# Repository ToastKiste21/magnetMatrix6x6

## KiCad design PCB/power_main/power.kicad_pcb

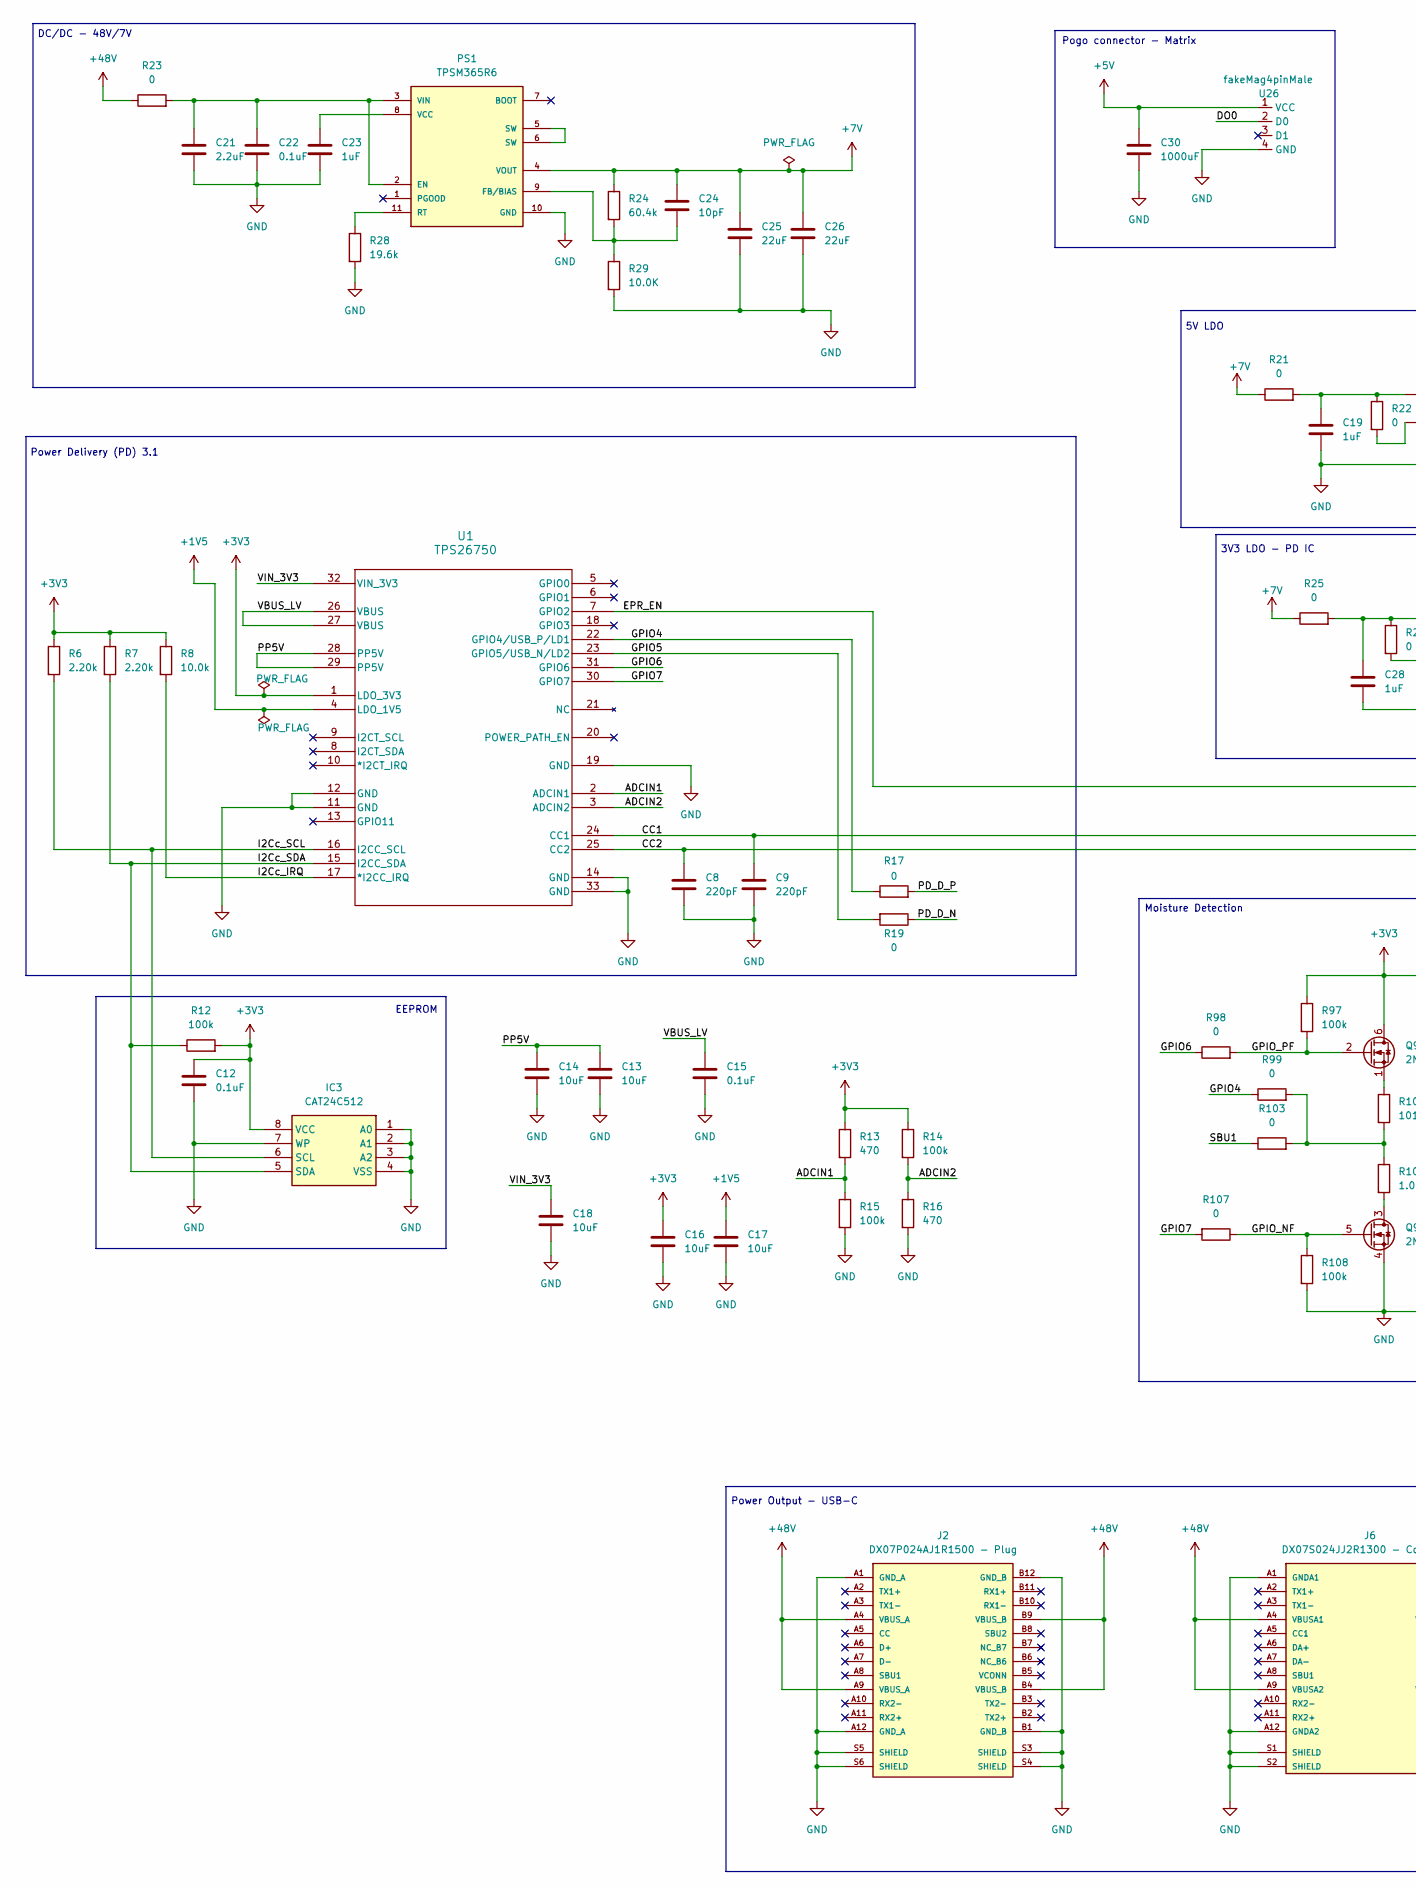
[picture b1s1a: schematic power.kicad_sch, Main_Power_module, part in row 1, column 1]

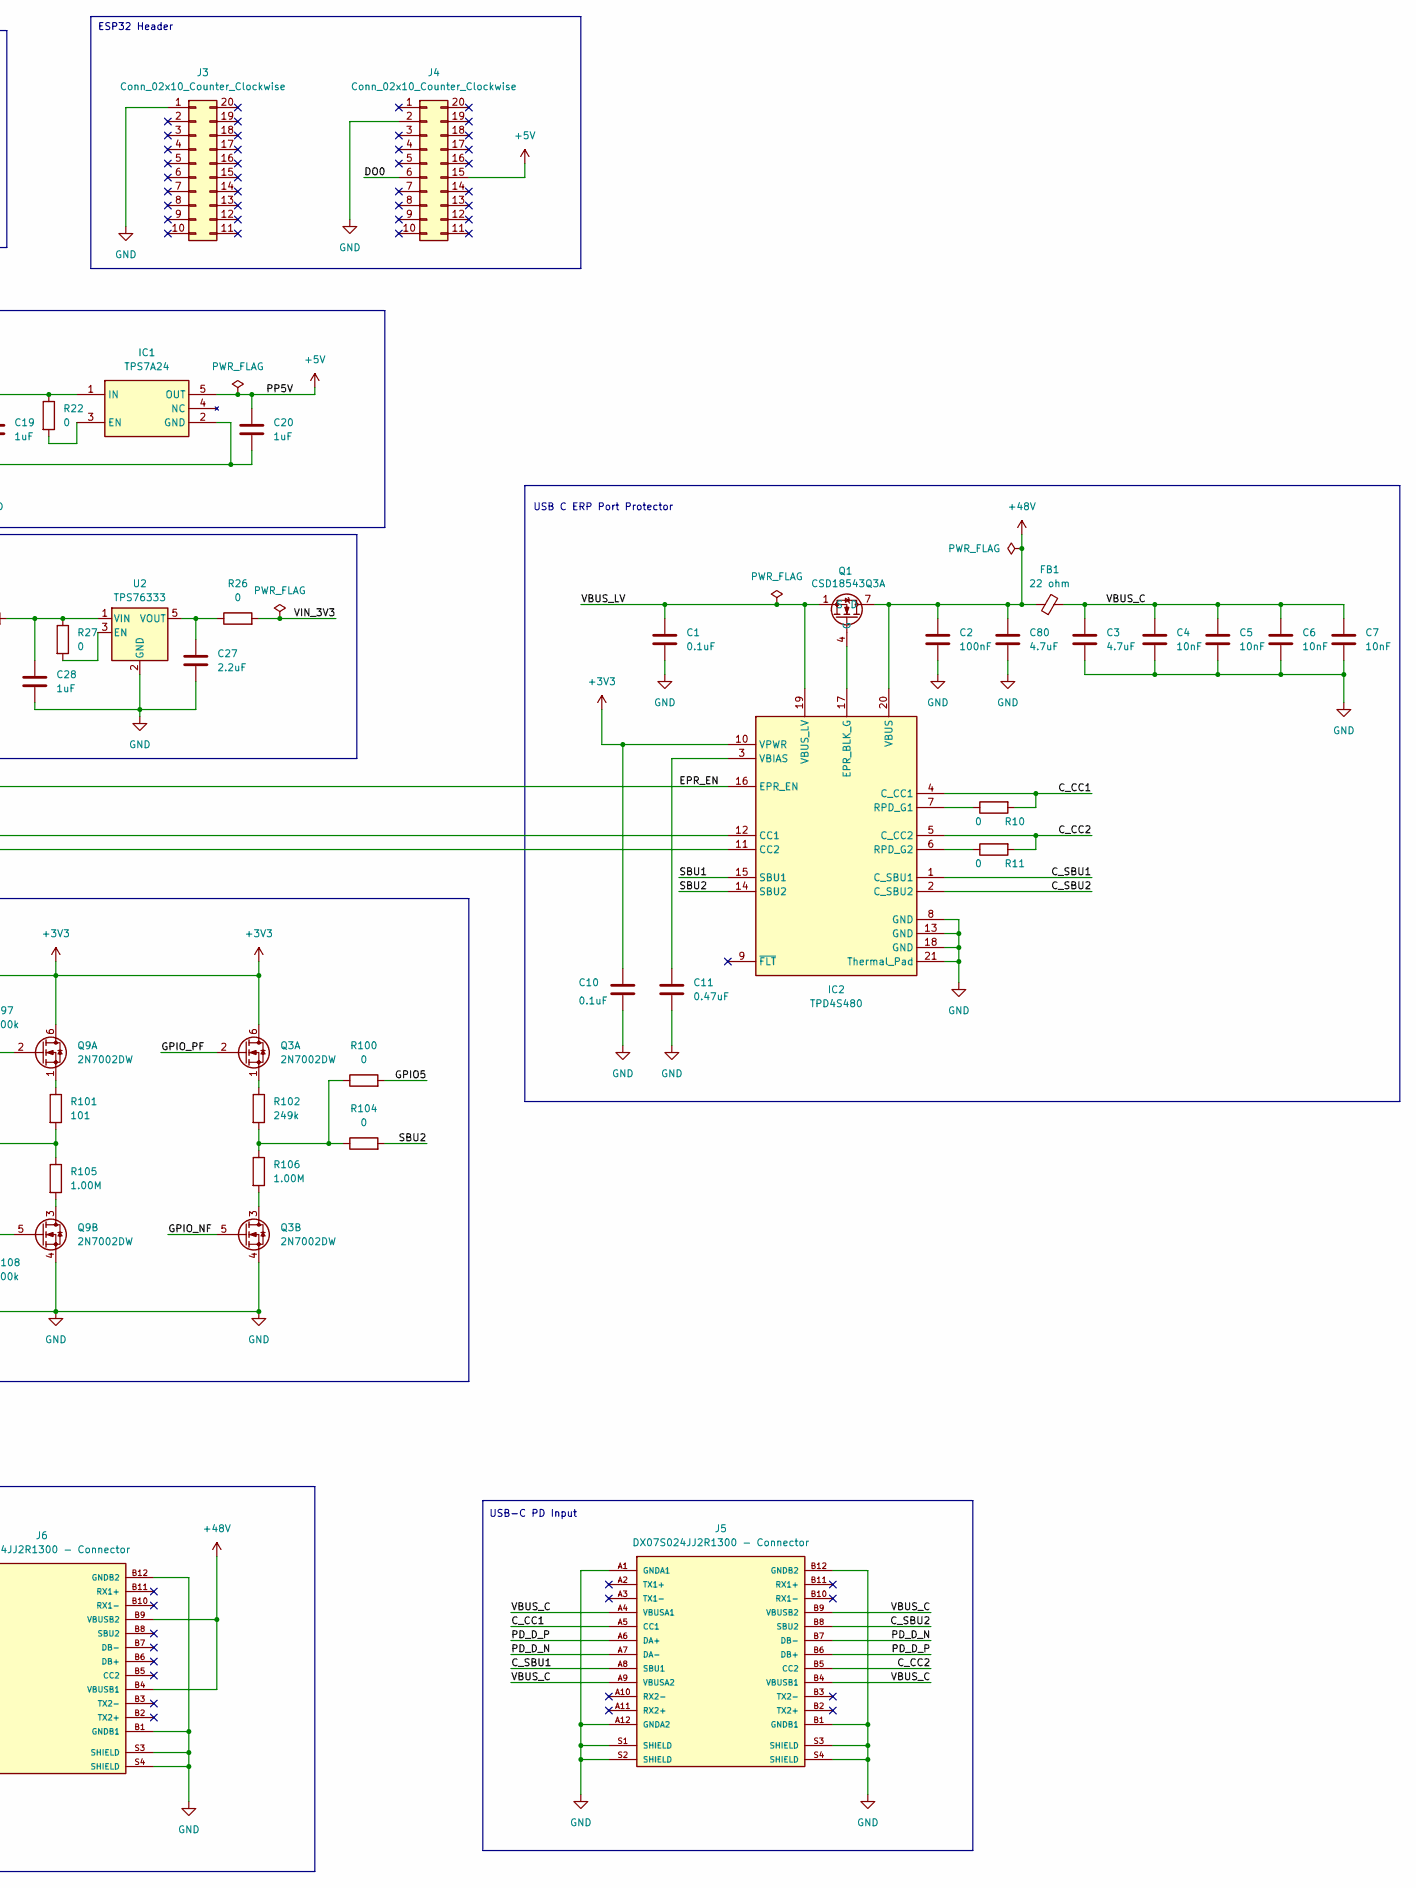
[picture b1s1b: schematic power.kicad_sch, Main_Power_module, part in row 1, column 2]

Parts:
C1, C10, C12, C15, C22: 0.1uF; C_0402_1005Metric
C2: 100nF; C_0201_0603Metric
C3, C80: 4.7uF; C_0805_2012Metric
C4, C5, C6, C7: 10nF; C_0603_1608Metric
C8, C9: 220pF; C_0201_0603Metric
C11: 0.47uF; C_0603_1608Metric
C13, C14: 10uF; C_0603_1608Metric
C16, C17, C18: 10uF; C_0402_1005Metric
C19, C20, C28: 1uF; C_0805_2012Metric
C21: 2.2uF; C_1206_3216Metric
C23: 1uF; C_0402_1005Metric
C24: 10pF; C_0402_1005Metric
C25, C26: 22uF; C_0603_1608Metric
C27: 2.2uF; C_0603_1608Metric
C30: 1000uF; CP_EIA-7343-15_Kemet-W
FB1: 22 ohm; L_0805_2012Metric
IC1: TPS7A24; SOT95P280X145-5N; Manufacturer_Part_Number TPS7A2450DBVR; Mouser Part Number 595-TPS7A2450DBVR
IC2: TPD4S480; QFN40P300X300X80-21N-D; Manufacturer_Part_Number TPD4S480RUKR
IC3: CAT24C512; SOIC127P600X175-8N; Manufacturer_Part_Number CAT24C512WI-GT3; Mouser Part Number 863-CAT24C512WI-GT3
J2: DX07P024AJ1R1500 - Plug; JAE_DX07P024AJ1R1500; PARTREV January 2016
J3, J4: Conn_02x10_Counter_Clockwise; PinHeader_2x10_P2.54mm_Vertical
J5, J6: DX07S024JJ2R1300 - Connector; JAE_DX07S024JJ2R1300; PARTREV 3
PS1: TPSM365R6; CONV_TPSM365R15RDNR; PARTREV A
Q1: CSD18543Q3A; Manufacturer_Part_Number CSD18543Q3A; Mouser Part Number 595-CSD18543Q3A
Q3, Q9: 2N7002DW; SOT-363_SC-70-6
R6, R7: 2.20k; R_0402_1005Metric
R8: 10.0k; R_0402_1005Metric
R10, R11, R17, R19, R21, R22, R23, R25, R26, R27: 0; R_0201_0603Metric
R12: 100k; R_0201_0603Metric
R13, R16: 470; R_0603_1608Metric
R14, R15: 100k; R_0603_1608Metric
R24: 60.4k; R_0603_1608Metric
R28: 19.6k; R_0402_1005Metric
R29: 10.0K; R_0402_1005Metric
R97, R108: 100k; R_0402_1005Metric
R98, R99, R100, R103, R104, R107: 0; R_0402_1005Metric
R101: 101; R_0603_1608Metric
R102: 249k; R_0603_1608Metric
R105, R106: 1.00M; R_0402_1005Metric
U1: TPS26750; VQFN32_RSM_TEX
U2: TPS76333; SOT-23-5
U26: fakeMag4pinMale; fakemag4pin90degMale; MPN MG0422F-RA

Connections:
+1V5: C17.1, U1.4 (LDO_1V5)
+3V3: C10.1, C12.1, C16.1, IC2.10 (VPWR), IC3.8 (VCC), Q3.6 (D), Q9.6 (D), R6.1, R7.1, R8.1, R12.2, R13.1, R14.1, R97.1, U1.1 (LDO_3V3)
+5V: C13.1, C14.1, C20.1, C30.1, IC1.5 (OUT), J4.15, U1.28 (PP5V), U1.29 (PP5V), U26.1 (VCC)
+7V: C24.1, C25.1, C26.1, PS1.4 (VOUT), PS1.4_1, PS1.4_2, PS1.4_3, PS1.4_4, PS1.4_5, R21.1, R24.1, R25.1
+48V: C2.1, C80.1, FB1.1, IC2.20 (VBUS), J2.A4 (VBUS_A), J2.A9 (VBUS_A), J2.B4 (VBUS_B), J2.B9 (VBUS_B), J6.A4 (VBUSA1), J6.A9 (VBUSA2), J6.B4 (VBUSB1), J6.B9 (VBUSB2), Q1.5 (D), Q1.6 (D), Q1.7 (D), Q1.8 (D), Q1.9 (D), R23.1
/ADCIN1: R13.2, R15.1, U1.2 (ADCIN1)
/ADCIN2: R14.2, R16.1, U1.3 (ADCIN2)
/CC1: C9.1, IC2.12 (CC1), U1.24 (CC1)
/CC2: C8.1, IC2.11 (CC2), U1.25 (CC2)
/C_CC1: IC2.4 (C_CC1), J5.A5 (CC1), R10.2
/C_CC2: IC2.5 (C_CC2), J5.B5 (CC2), R11.2
/C_SBU1: IC2.1 (C_SBU1), J5.A8 (SBU1)
/C_SBU2: IC2.2 (C_SBU2), J5.B8 (SBU2)
/DO0: J4.6, U26.2 (D0)
/EPR_EN: IC2.16 (EPR_EN), U1.7 (GPIO2)
/GPIO4: R17.1, R99.1, U1.22 (GPIO4/USB_P/LD1)
/GPIO5: R19.2, R100.2, U1.23 (GPIO5/USB_N/LD2)
/GPIO6: R98.1, U1.31 (GPIO6)
/GPIO7: R107.2, U1.30 (GPIO7)
/GPIO_NF: Q3.5 (G), Q9.5 (G), R107.1, R108.1
/GPIO_PF: Q3.2 (G), Q9.2 (G), R97.2, R98.2
/I2Cc_IRQ: R8.2, U1.17 (*I2CC_IRQ)
/I2Cc_SCL: IC3.6 (SCL), R6.2, U1.16 (I2CC_SCL)
/I2Cc_SDA: IC3.5 (SDA), R7.2, R12.1, U1.15 (I2CC_SDA)
/PD_D_N: J5.A7 (DA-), J5.B7 (DB-), R19.1
/PD_D_P: J5.A6 (DA+), J5.B6 (DB+), R17.2
/SBU1: IC2.15 (SBU1), R103.1
/SBU2: IC2.14 (SBU2), R104.2
/VBUS_C: C3.1, C4.1, C5.1, C6.1, C7.1, FB1.2, J5.A4 (VBUSA1), J5.A9 (VBUSA2), J5.B4 (VBUSB1), J5.B9 (VBUSB2)
/VBUS_LV: C1.1, C15.1, IC2.19 (VBUS_LV), Q1.1 (S), Q1.2 (S), Q1.3 (S), U1.26 (VBUS), U1.27 (VBUS)
/VIN_3V3: C18.1, R26.2, U1.32 (VIN_3V3)
GND: C1.2, C2.2, C3.2, C4.2, C5.2, C6.2, C7.2, C8.2, C9.2, C10.2, C11.2, C12.2, C13.2, C14.2, C15.2, C16.2, C17.2, C18.2, C19.2, C20.2, C21.2, C22.2, C23.2, C25.2, C26.2, C27.2, C28.2, C30.2, C80.2, IC1.2 (GND), IC2.8 (GND), IC2.13 (GND), IC2.18 (GND), IC2.21 (Thermal_Pad), IC3.1 (A0), IC3.2 (A1), IC3.3 (A2), IC3.4 (VSS), IC3.7 (WP), J2.A1 (GND_A), J2.A12 (GND_A), J2.B1 (GND_B), J2.B12 (GND_B), J2.S3 (SHIELD), J2.S4 (SHIELD), J2.S5 (SHIELD), J2.S6 (SHIELD), J3.1 (GND), J4.2, J5.A1 (GNDA1), J5.A12 (GNDA2), J5.B1 (GNDB1), J5.B12 (GNDB2), J5.S1 (SHIELD), J5.S2 (SHIELD), J5.S3 (SHIELD), J5.S4 (SHIELD), J6.A1 (GNDA1), J6.A12 (GNDA2), J6.B1 (GNDB1), J6.B12 (GNDB2), J6.S1 (SHIELD), J6.S2 (SHIELD), J6.S3 (SHIELD), J6.S4 (SHIELD), PS1.10 (GND), PS1.10_1, PS1.10_2, PS1.10_3, PS1.10_4, PS1.10_5, Q3.4 (S), Q9.4 (S), R15.2, R16.2, R28.2, R29.2, R108.2, U1.11 (GND), U1.12 (GND), U1.14 (GND), U1.19 (GND), U1.33 (GND), U2.2 (GND), U26.4 (GND)
unnamed: IC1.3 (EN), R22.2
unnamed: C19.1, IC1.1 (IN), R21.2, R22.1
unnamed: IC2.17 (EPR_BLK_G), Q1.4 (G)
unnamed: IC2.7 (RPD_G1), R10.1
unnamed: IC2.6 (RPD_G2), R11.1
unnamed: C11.1, IC2.3 (VBIAS)
unnamed: C21.1, C22.1, PS1.2 (EN), PS1.3 (VIN), PS1.3_1, R23.2
unnamed: C24.2, PS1.9 (FB/BIAS), R24.2, R29.1
unnamed: PS1.11 (RT), R28.1
unnamed: PS1.5 (SW), PS1.5_1, PS1.5_2, PS1.5_3, PS1.5_4, PS1.5_5, PS1.6 (SW), PS1.6_1, PS1.6_2
unnamed: C23.1, PS1.8 (VCC)
unnamed: Q3.1 (S), R102.1
unnamed: Q3.3 (D), R106.2
unnamed: Q9.1 (S), R101.1
unnamed: Q9.3 (D), R105.2
unnamed: R100.1, R102.2, R104.1, R106.1
unnamed: R99.2, R101.2, R103.2, R105.1
unnamed: R27.2, U2.3 (EN)
unnamed: C28.1, R25.2, R27.1, U2.1 (VIN)
unnamed: C27.1, R26.1, U2.5 (VOUT)

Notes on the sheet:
Power Output - USB-C
DC/DC - 48V/7V
USB C ERP Port Protector
Power Delivery (PD) 3.1
5V LDO
Pogo connector - Matrix
3V3 LDO - PD IC
EEPROM
ESP32 Header
USB-C PD Input
Moisture Detection

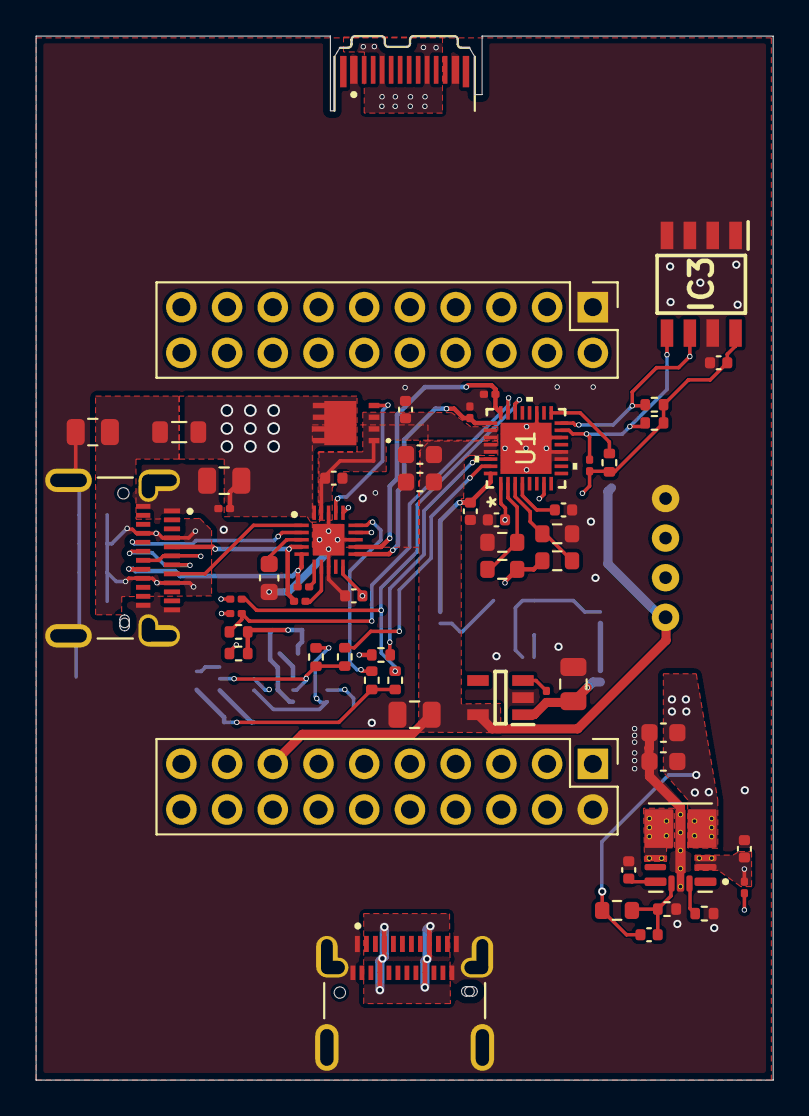
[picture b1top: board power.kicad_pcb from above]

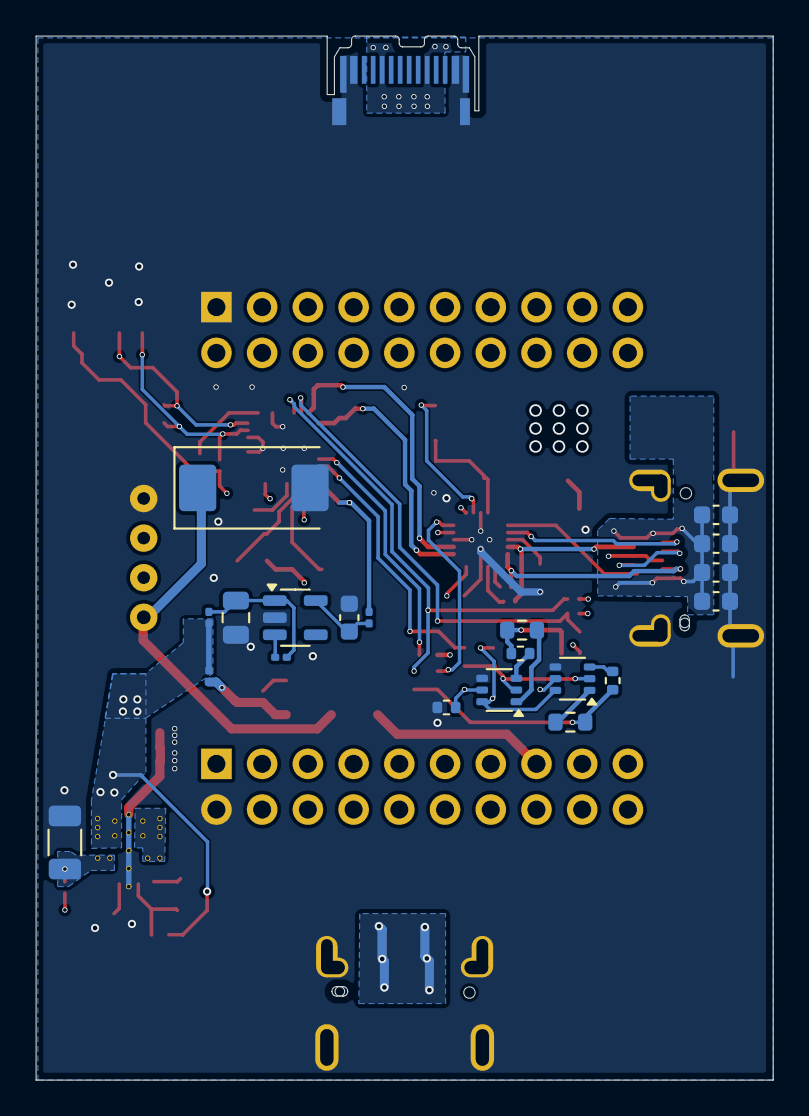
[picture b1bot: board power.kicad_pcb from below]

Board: 4 copper layers, 40.9 x 58.0 mm, 79 parts (20 on the bottom side), 52 nets.

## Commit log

2025-06-22 add power module to power max 240W of LEDs (USB-C PD 3.1)
2025-06-23 add missing GPIO_PF small trace refactoring
2025-06-24 removed POWER_PATH_EN logic add more doku and pictires for context
2025-06-24 add footprint placements
